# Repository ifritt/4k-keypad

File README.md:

# 4k-keypad
 repository for all keypad designs
  - 4-key keypad
  - 4-key keypad arduino nano
  - 4-key keypad esp32

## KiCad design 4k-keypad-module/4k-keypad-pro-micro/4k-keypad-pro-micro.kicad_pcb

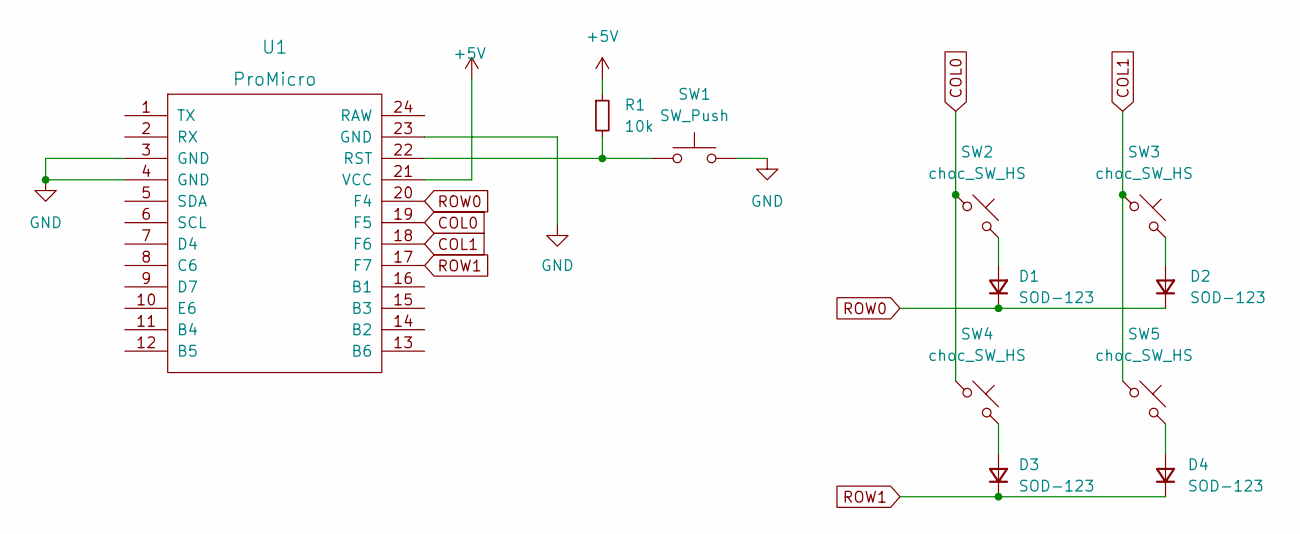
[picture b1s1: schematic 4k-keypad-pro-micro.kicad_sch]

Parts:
D1, D2, D3, D4: SOD-123; D_SOD-123
R1: 10k; R_0805_2012Metric
SW1: SW_Push; SKQG-1155865
SW2, SW3, SW4, SW5: choc_SW_HS; SW_choc_HS_1u
U1: ProMicro

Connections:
+5V: R1.1, U1.21 (VCC)
COL0: SW2.1, SW4.1, U1.19 (F5)
COL1: SW3.1, SW5.1, U1.18 (F6)
GND: SW1.2, U1.3 (GND), U1.4 (GND), U1.23 (GND)
unnamed: D1.2 (A), SW2.2
unnamed: D2.2 (A), SW3.2
unnamed: D3.2 (A), SW4.2
unnamed: D4.2 (A), SW5.2
unnamed: R1.2, SW1.1, U1.22 (RST)
ROW0: D1.1 (K), D2.1 (K), U1.20 (F4)
ROW1: D3.1 (K), D4.1 (K), U1.17 (F7)

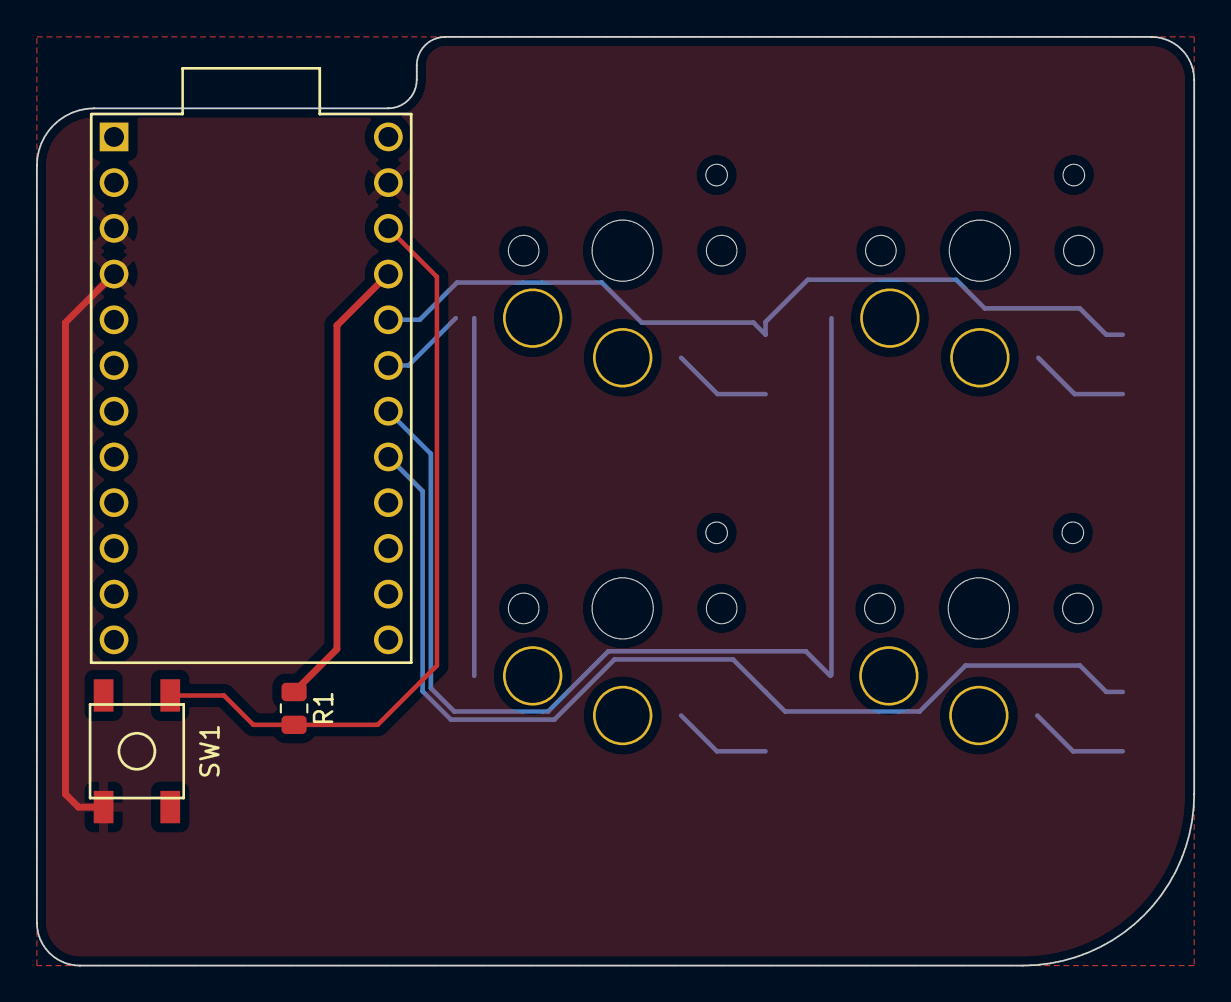
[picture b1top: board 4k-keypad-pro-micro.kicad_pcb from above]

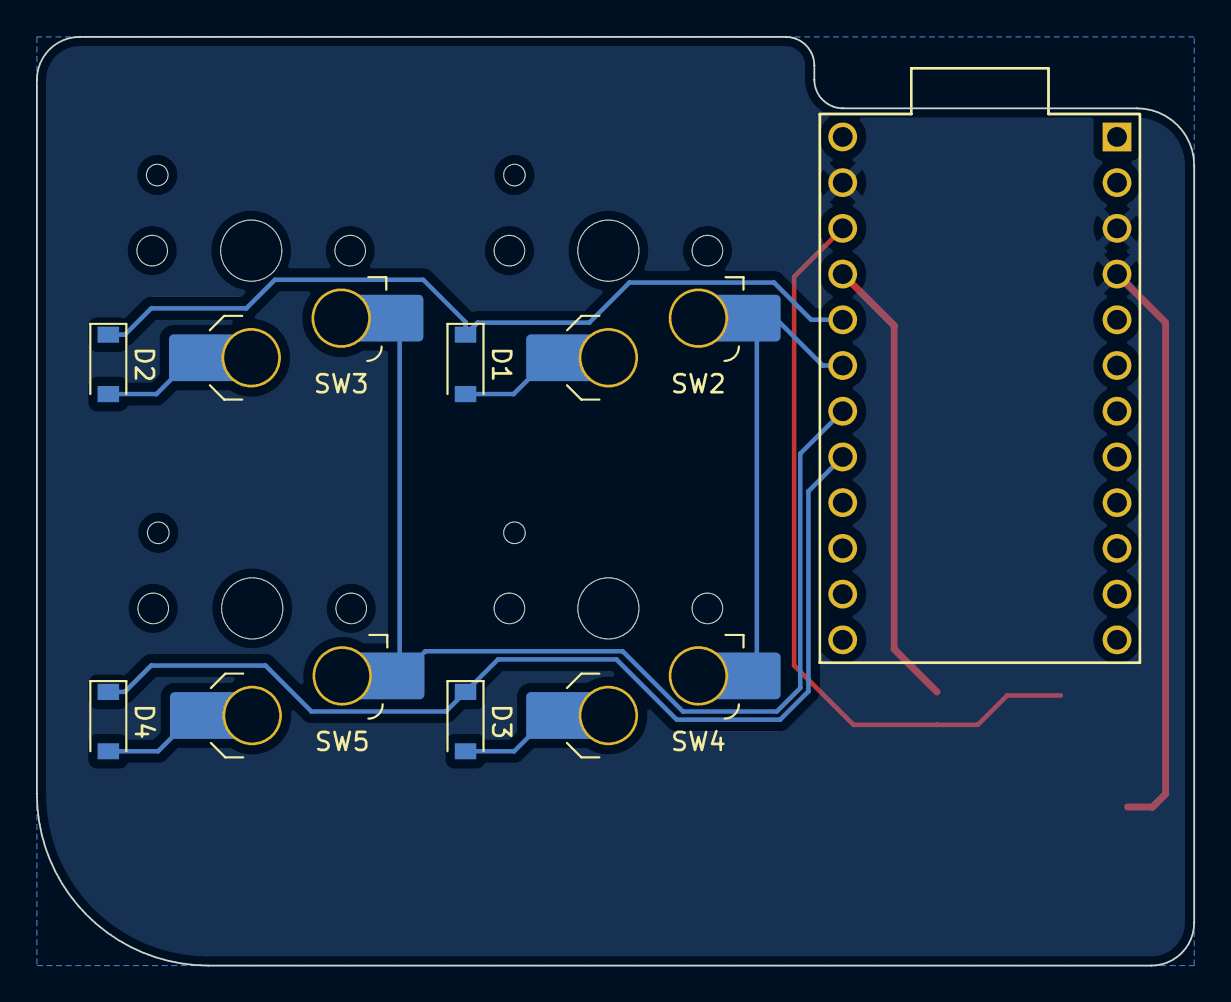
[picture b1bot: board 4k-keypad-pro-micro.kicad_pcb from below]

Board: 2 copper layers, 64.3 x 51.6 mm, 11 parts (8 on the bottom side), 11 nets.

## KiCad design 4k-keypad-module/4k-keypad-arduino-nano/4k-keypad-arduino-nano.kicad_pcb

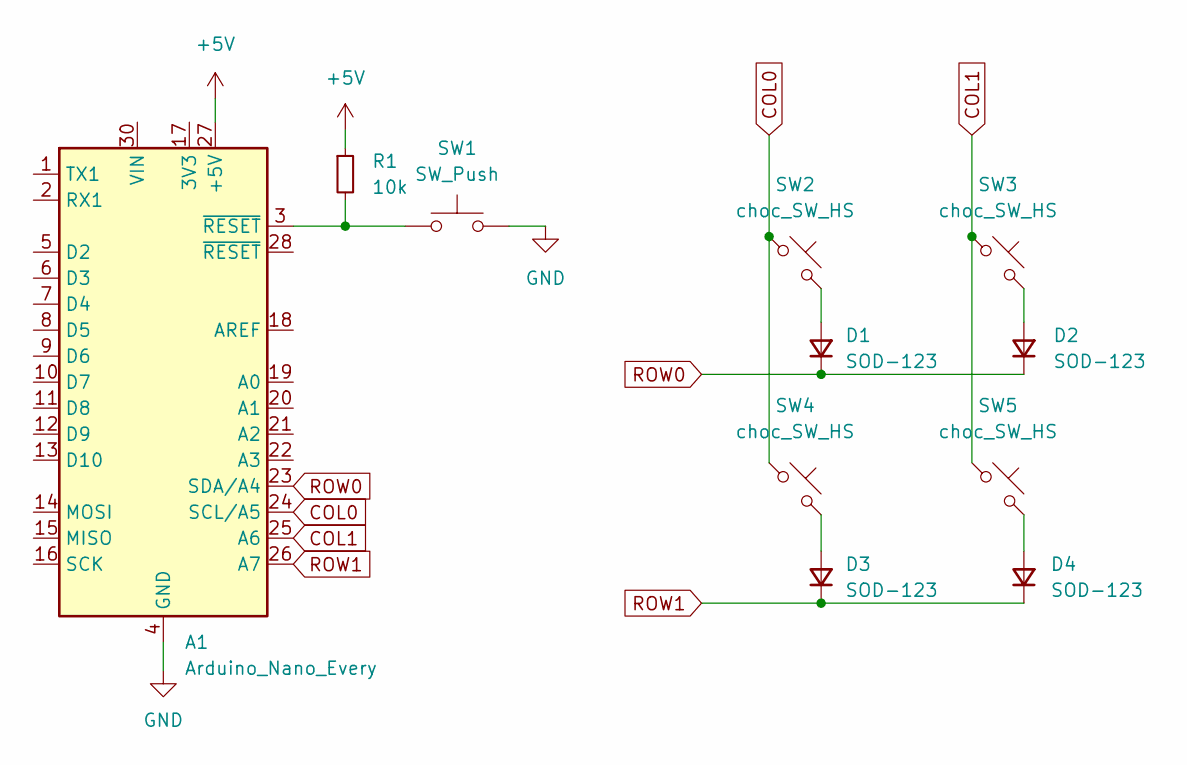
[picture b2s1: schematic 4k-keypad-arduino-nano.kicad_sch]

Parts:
A1: Arduino_Nano_Every; Arduino_Nano
D1, D2, D3, D4: SOD-123; D_SOD-123
R1: 10k; R_0805_2012Metric
SW1: SW_Push; SKQG-1155865
SW2, SW3, SW4, SW5: choc_SW_HS; SW_choc_HS_1u

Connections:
+5V: A1.27 (+5V), R1.1
COL0: A1.24 (SCL/A5), SW2.1, SW4.1
COL1: A1.25 (A6), SW3.1, SW5.1
GND: A1.4 (GND), A1.29 (GND), SW1.2
unnamed: A1.3 (~RESET), R1.2, SW1.1
unnamed: D1.2 (A), SW2.2
unnamed: D2.2 (A), SW3.2
unnamed: D3.2 (A), SW4.2
unnamed: D4.2 (A), SW5.2
ROW0: A1.23 (SDA/A4), D1.1 (K), D2.1 (K)
ROW1: A1.26 (A7), D3.1 (K), D4.1 (K)

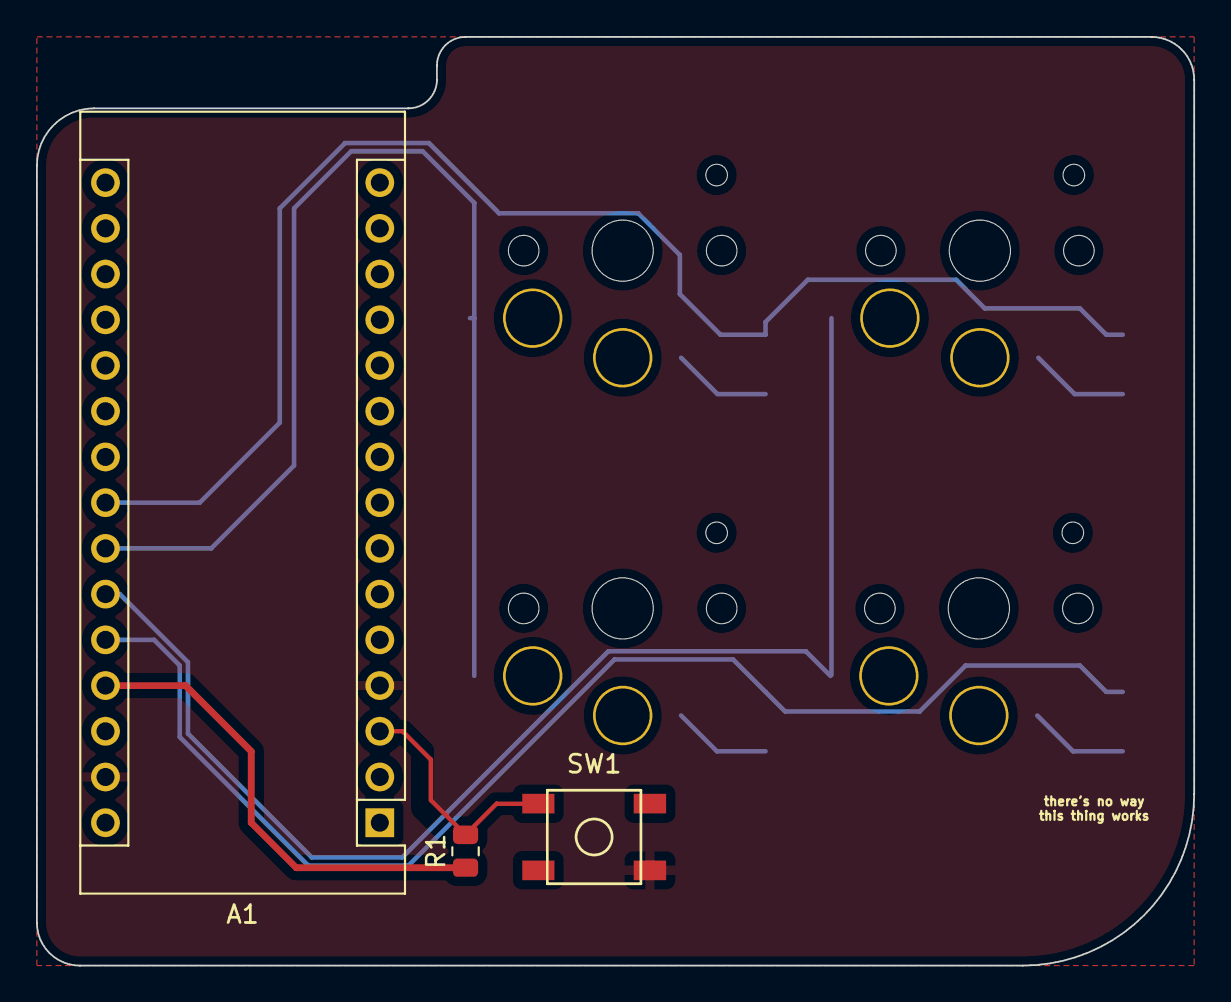
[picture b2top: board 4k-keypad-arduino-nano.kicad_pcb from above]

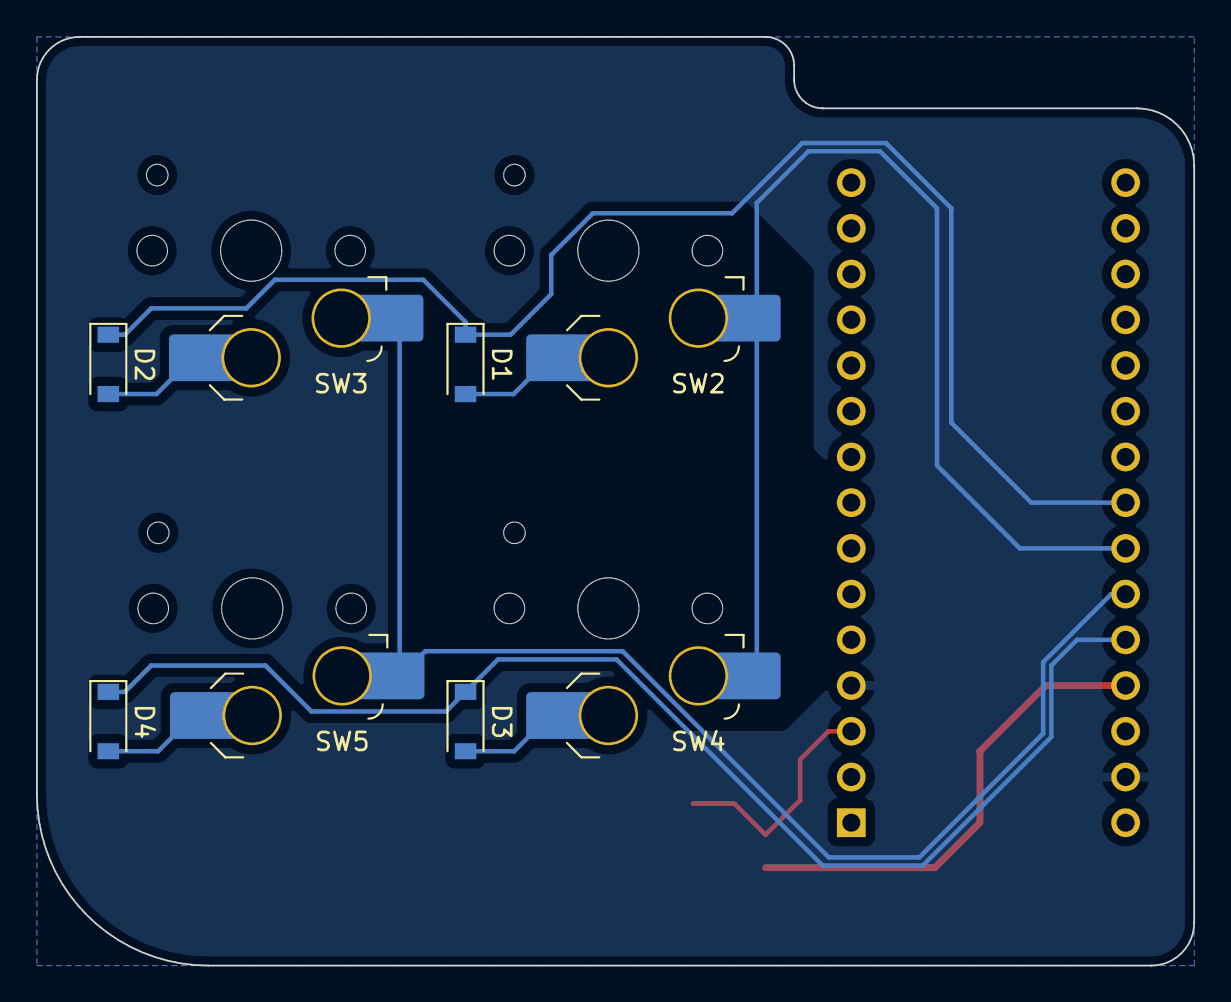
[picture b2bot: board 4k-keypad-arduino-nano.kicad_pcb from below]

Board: 2 copper layers, 64.3 x 51.6 mm, 11 parts (8 on the bottom side), 11 nets.

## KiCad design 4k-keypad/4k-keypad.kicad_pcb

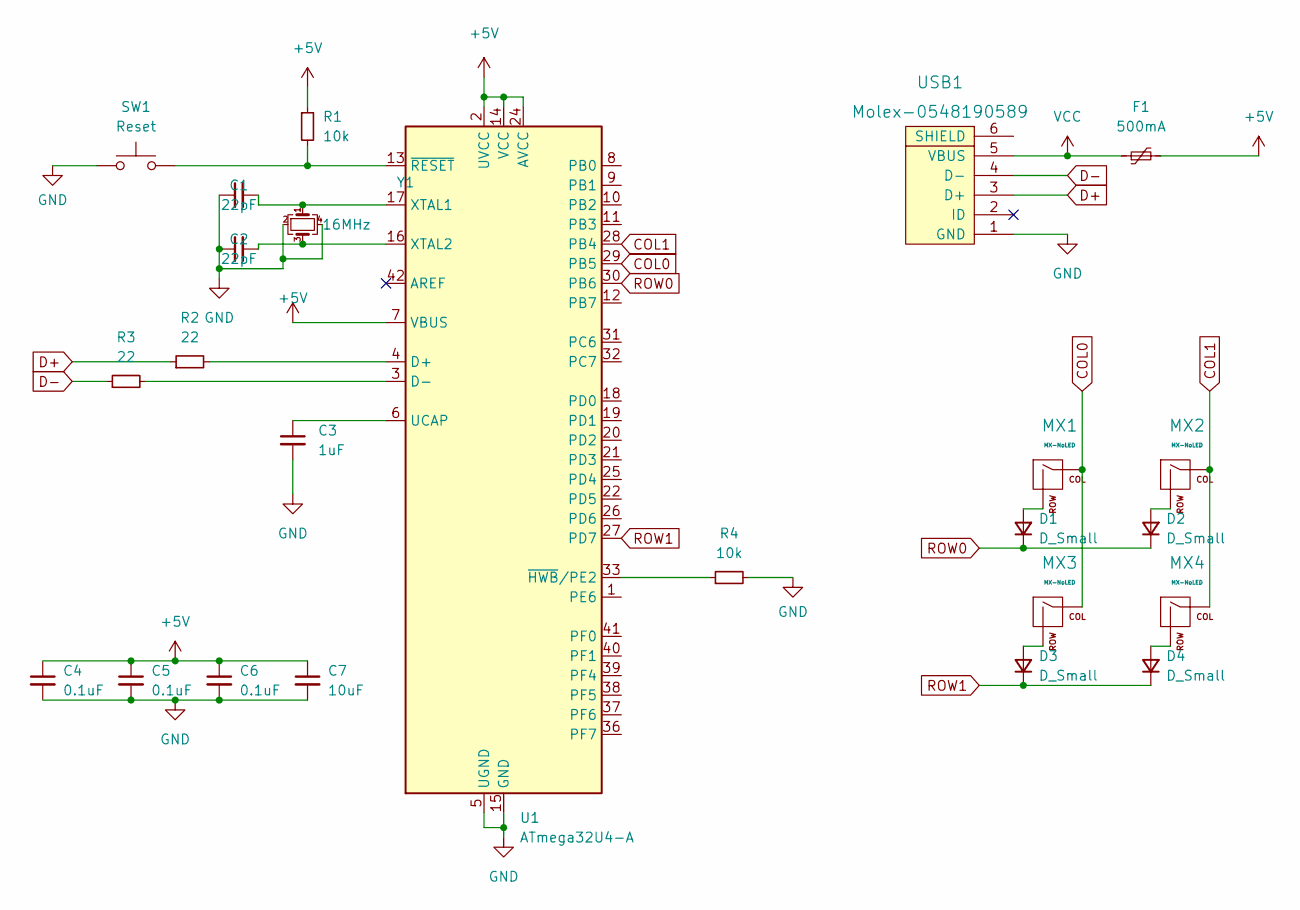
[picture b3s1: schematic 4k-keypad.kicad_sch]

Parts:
C1, C2: 22pF; C_0805_2012Metric
C3: 1uF; C_0805_2012Metric
C4, C5, C6: 0.1uF; C_0805_2012Metric
C7: 10uF; C_0805_2012Metric
D1, D2, D3, D4: D_Small; D_SOD-123
F1: 500mA; Fuse_1206_3216Metric
MX1, MX2, MX3, MX4: MX-NoLED; KailhChoc-1U
R1, R4: 10k; R_0805_2012Metric
R2, R3: 22; R_0805_2012Metric
SW1: Reset; SKQG-1155865
U1: ATmega32U4-A; TQFP-44_10x10mm_P0.8mm
USB1: Molex-0548190589
Y1: 16MHz; Crystal_SMD_3225-4Pin_3.2x2.5mm

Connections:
+5V: C4.1, C5.1, C6.1, C7.1, F1.2, R1.1, U1.2 (UVCC), U1.7 (VBUS), U1.14 (VCC), U1.24 (AVCC), U1.34 (VCC), U1.44 (AVCC)
COL0: MX1.1 (COL), MX3.1 (COL), U1.29 (PB5)
COL1: MX2.1 (COL), MX4.1 (COL), U1.28 (PB4)
D+: R2.1, USB1.3 (D+)
D-: R3.1, USB1.4 (D-)
GND: C1.1, C2.1, C3.2, C4.2, C5.2, C6.2, C7.2, R4.2, SW1.1, U1.5 (UGND), U1.15 (GND), U1.23 (GND), U1.35 (GND), U1.43 (GND), USB1.1 (GND), Y1.2, Y1.4
unnamed: C1.2, U1.17 (XTAL1), Y1.1
unnamed: C2.2, U1.16 (XTAL2), Y1.3
unnamed: C3.1, U1.6 (UCAP)
unnamed: D1.2 (A), MX1.2 (ROW)
unnamed: D2.2 (A), MX2.2 (ROW)
unnamed: D3.2 (A), MX3.2 (ROW)
unnamed: D4.2 (A), MX4.2 (ROW)
unnamed: R1.2, SW1.2, U1.13 (~RESET)
unnamed: R2.2, U1.4 (D+)
unnamed: R3.2, U1.3 (D-)
unnamed: R4.1, U1.33 (~HWB/PE2)
ROW0: D1.1 (K), D2.1 (K), U1.30 (PB6)
ROW1: D3.1 (K), D4.1 (K), U1.27 (PD7)
VCC: F1.1, USB1.5 (VBUS)

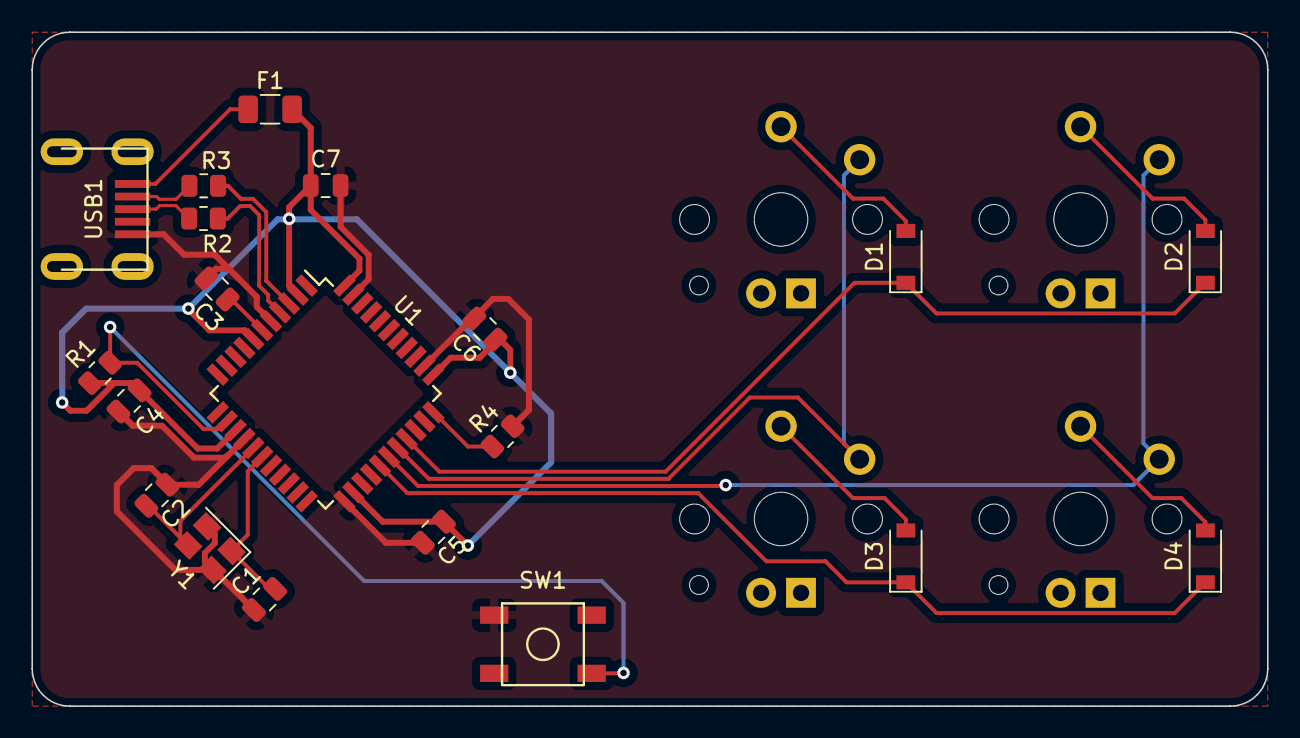
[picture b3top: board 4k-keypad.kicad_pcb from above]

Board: 2 copper layers, 78.6 x 42.9 mm, 24 parts (0 on the bottom side), 20 nets.

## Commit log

2022-09-26 initialize
2022-09-26 add submodules
2022-09-26 add footprint libs
2022-09-26 schematic
2022-09-29 update commit
2022-09-29 fixed
2023-12-12 merged
